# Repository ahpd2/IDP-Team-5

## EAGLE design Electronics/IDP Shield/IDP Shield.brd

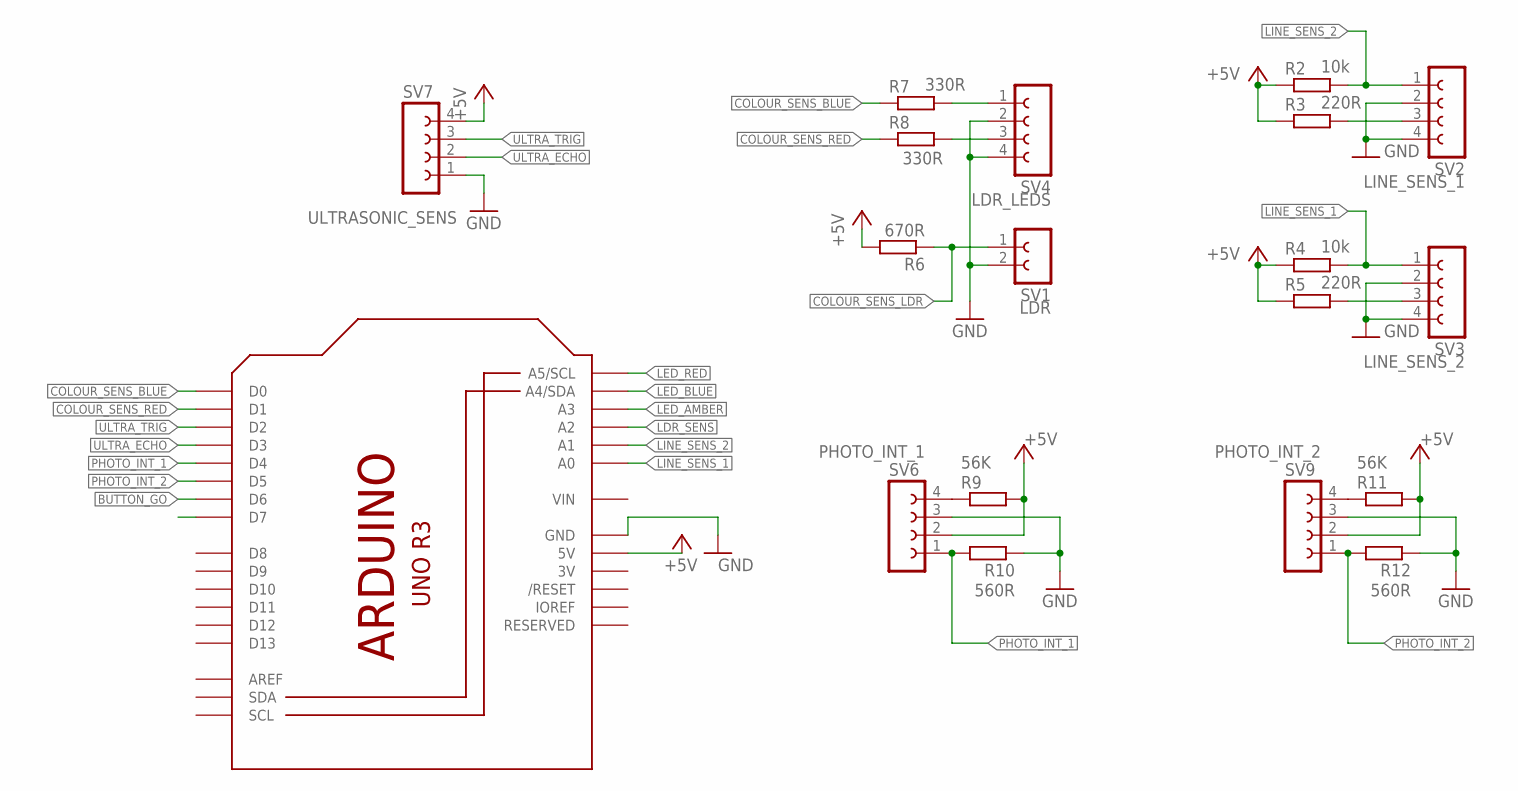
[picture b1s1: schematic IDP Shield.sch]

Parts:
M1: IDP_PROTOBOARD; IDP_PROTO
R2, R4: 10k; 0207/10
R3, R5: 220R; 0207/10
R6: 670R; 0207/10
R7, R8: 330R; 0207/10
R9, R11: 56K; 0207/10
R10, R12: 560R; 0207/10
SV1: LDR; FE02-1
SV2: LINE_SENS_1; FE04-1
SV3: LINE_SENS_2; FE04-1
SV4: LDR_LEDS; FE04-1
SV6: PHOTO_INT_1; FE04-1
SV7: ULTRASONIC_SENS; FE04-1
SV9: PHOTO_INT_2; FE04-1

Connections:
3V: M1.3V
+5V: M1.5V, M1.5V@0 (5V), M1.5V@1 (5V), M1.5V@2 (5V), M1.5V@3 (5V), M1.5V@4 (5V), M1.5V@5 (5V), M1.5V@6 (5V), M1.5V@7 (5V), M1.5V@8 (5V), M1.5V@9 (5V), M1.5V@10 (5V), M1.5V@11 (5V), M1.5V@12 (5V), M1.5V@13 (5V), M1.5V@14 (5V), M1.5V@15 (5V), M1.5V@16 (5V), M1.5V@17 (5V), M1.5V@18 (5V), M1.5V@19 (5V), M1.5V@20 (5V), M1.5V@21 (5V), M1.5V@22 (5V), M1.5V@23 (5V), M1.5V@24 (5V), M1.5V@25 (5V), M1.5V@26 (5V), M1.5V@27 (5V), M1.5V@28 (5V), M1.5V@29 (5V), M1.5V@30 (5V), M1.5V@31 (5V), M1.5V@32 (5V), M1.5V@33 (5V), M1.5V@34 (5V), M1.5V@35 (5V), M1.5V@36 (5V), M1.5V@37 (5V), M1.5V@38 (5V), M1.5V@39 (5V), M1.5V@40 (5V), R2.1, R3.1, R4.1, R5.1, R6.2, R9.2, R11.2, SV6.2, SV7.4, SV9.2
BUTTON_GO: M1.D6
COLOUR_SENS_BLUE: M1.D0, R7.1
COLOUR_SENS_LDR: R6.1, SV1.1
COLOUR_SENS_RED: M1.D1, R8.1
GND: M1.GND, M1.GND16 (GND), M1.GND17 (GND), M1.GND18 (GND), M1.GND19 (GND), M1.GND20 (GND), M1.GND21 (GND), M1.GND22 (GND), M1.GND23 (GND), M1.GND24 (GND), M1.GND25 (GND), M1.GND@1 (GND), M1.GND@2 (GND), M1.GND@3 (GND), M1.GND@4 (GND), M1.GND@5 (GND), M1.GND@6 (GND), M1.GND@7 (GND), M1.GND@8 (GND), M1.GND@9 (GND), M1.GND@10 (GND), M1.GND@11 (GND), M1.GND@12 (GND), M1.GND@13 (GND), M1.GND@14 (GND), M1.GND@15 (GND), M1.GND@26 (GND), M1.GND@27 (GND), M1.GND@28 (GND), M1.GND@29 (GND), M1.GND@30 (GND), M1.GND@31 (GND), M1.GND@32 (GND), M1.GND@33 (GND), M1.GND@34 (GND), M1.GND@35 (GND), M1.GND@36 (GND), M1.GND@37 (GND), M1.GND@38 (GND), M1.GND@39 (GND), M1.GND@40 (GND), M1.GND@41 (GND), M1.GND@42 (GND), M1.GND@43 (GND), M1.GND@44 (GND), M1.GND@45 (GND), M1.GND@46 (GND), M1.GND@47 (GND), M1.GND@48 (GND), R10.2, R12.2, SV1.2, SV2.2, SV2.4, SV3.2, SV3.4, SV4.2, SV4.4, SV6.3, SV7.1, SV9.3
LDR_SENS: M1.A2
LED_AMBER: M1.A3
LED_BLUE: M1.A4 (A4/SDA)
LED_RED: M1.A5 (A5/SCL)
LINE_SENS_1: M1.A0, R4.2, SV3.1
LINE_SENS_2: M1.A1, R2.2, SV2.1
unnamed: R7.2, SV4.1
unnamed: R3.2, SV2.3
unnamed: R8.2, SV4.3
unnamed: R5.2, SV3.3
unnamed: R9.1, SV6.4
unnamed: R11.1, SV9.4
PHOTO_INT_1: M1.D4, R10.1, SV6.1
PHOTO_INT_2: M1.D5, R12.1, SV9.1
ULTRA_ECHO: M1.D3, SV7.2
ULTRA_TRIG: M1.D2, SV7.3

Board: 2 copper layers, 19 parts (0 on the bottom side), 17 nets, no tracks yet.

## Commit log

2020-11-06 Add gitignores
2020-11-06 Create Shield schematic base
2020-11-08 OpenCV initial commit
2020-11-08 Add basic components
2020-11-09 Add c optimised functions
2020-11-16 Add low level code for motors and sensors
2020-11-19 Expand low level code
2020-11-20 Update schematics
2020-11-20 Add Line and distance sensor read functions
2020-11-20 code for first right turn added
2020-11-21 Pseudo code for delivery strategy
2020-11-21 Added more pseudocode to delivery
2020-11-21 comment test
2020-11-21 Testing, added a comment
2020-11-22 Block detection and delivery without computer vision, partially complete
2020-11-22 Object delivery code complete
2020-11-23 Working line following
2020-11-23 code for moving round in CIRCLE added
2020-11-24 Add vscode arduino integration
2020-11-24 Format + Document code
2020-11-24 Double checking object in front added, Goes back to start if all objects delivered
2020-11-24 Edited finish condition
2020-11-24 Flashing Amber LED
2020-11-24 Improve avoidance capabilities
2020-11-25 Blue delivery added
2020-11-25 Fixing Blue delivery
2020-11-25 First competition - leaving blue blocks aside
2020-11-26 improve colour sensor reading
2020-11-27 final changes for first competition
2020-11-27 Add VSCODE intellisense macros
2020-11-28 Work on Blue Delivery
2020-11-30 State based overhaul
2020-11-30 Move to switch statement, remove obselete code
2020-11-30 Minor bug fixes on delivery logic
2020-11-30 updated line follower thresholds
2020-11-30 simplify last delivered is red logic
2020-12-01 Fix logical/operational bugs. still slow
2020-12-12 Rename Low_Level_Code.ino to Main_Code.ino
2020-12-12 Rename Effetors.ino to Effetocrs.ino
2020-12-12 Rename Effetocrs.ino to Effectors.ino
2020-12-12 Changed Name of Main file
2020-12-13 small additional comments made
2020-12-13 Final changes made
